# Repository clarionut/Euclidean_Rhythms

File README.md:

# Euclidean Rhythms

This repository contains details of my derivative of [Hagiwo's Euclidean Rhythms](https://note.com/solder_state/n/n433b32ea6dbc) synthesiser module.

In his notes about the module, Hagiwo comments that there is considerable latency due to the OLED display and also mentions instability in the program
possibly caused by memory issues. He partially addresses the latency issue by only updating the OLED on clock inputs, but this makes it difficult to
update the settings in the absence of a clock input.
During analysis of the code I found several things which would compound these issues, e.g.
- use of a relatively slow I2C OLED display. Swapped for an alternative using much faster hardware SPI
- (using a graphics library which keeps an in-memory copy of the display. Changed to the less memory-intensive U8glib library). Subsequent testing has shown that code using the Adafruit_SSD1306 library runs roughly twice as fast as either u8glib or u8g2. I'd therefore recommend using the EuclideanRhythms_AF sketch. It's larger than the u8glib based code but has shown no signs of instability despite its greater functionality
- the original code uses multiple loops over the channels, each processing a single aspect of the code. Restructured to carry out as many of these
operations as possible in a single loop
- use of the Arduino digitalWrite() function (intrinsically very slow) to output the triggers. Replaced by direct port operations to update all trigger
outputs much faster and simultaneously
- the rotary encoder originally used both interrupt pins of the Arduino with simple polling of the clock input, potentially leading to short clock pulses
being missed. The Encoder library can also be used in a single-interrupt mode allowing the clock input to use the other interrupt, with the interrupt
service routine directly generating the trigger outputs

These changes significantly improve the performance and allow the display to be updated on each clock and when the rotary encoder is used. The display
update is still relatively slow even using hardware SPI resulting in long & variable length trigger outputs. Also the OLED is always on even if the
module is not in use. I therefore added a screensaver which blanks the OLED after 30 seconds plus LEDs to monitor the trigger outputs. The OLED is
enabled again when the rotary encoder is used. This allows quite high clock speeds once the screensaver has kicked in.

Some extra functionality has been added to the code:
- ability to 'Put' the current settings into the Arduino EEPROM and 'Get' them from EEPROM in a subsequent session. This version of the code starts up
with predefined default settings, but it would be easy to modify so that the stored settings are retrieved automatically at start up
- a probability control by potentiometer or input CV to vary the likelyhood of changes in Random mode. As in Hagiwo's original code the allowed ranges
of randomness are predefined in the code with the probability controls influencing how likely the changes are
- option for a gate input to re-zero all the output channels to the starting position. I didn't implement this hardware due to a lack of space on my
Eurorack panel but the code for it is present

There are some more details of the changes in the Arduino code comments. The hardware is similar to the original but uses an Arduino Pro Mini rather than
a Nano, has buffering on the outputs for protection and to give higher voltage triggers, and has additional circuitry for the probability controls &
manual step button.

Please note that I built this module using stripboard rather than a PCB. The KiCad files and Gerbers have been used to build an [SPI version of Hagiwo's 6-channel trigger sequencer](https://github.com/clarionut/6-channel-trg-sequencer) so the PCB layout has now been verified apart from the probability CV input section.

### Updates
08-10-2025 - updated KiCad files (amended silk-screen labelling, minor header-pin changes); added Arduino code using the faster Adafruit_SSD1306 library - RECOMMENDED

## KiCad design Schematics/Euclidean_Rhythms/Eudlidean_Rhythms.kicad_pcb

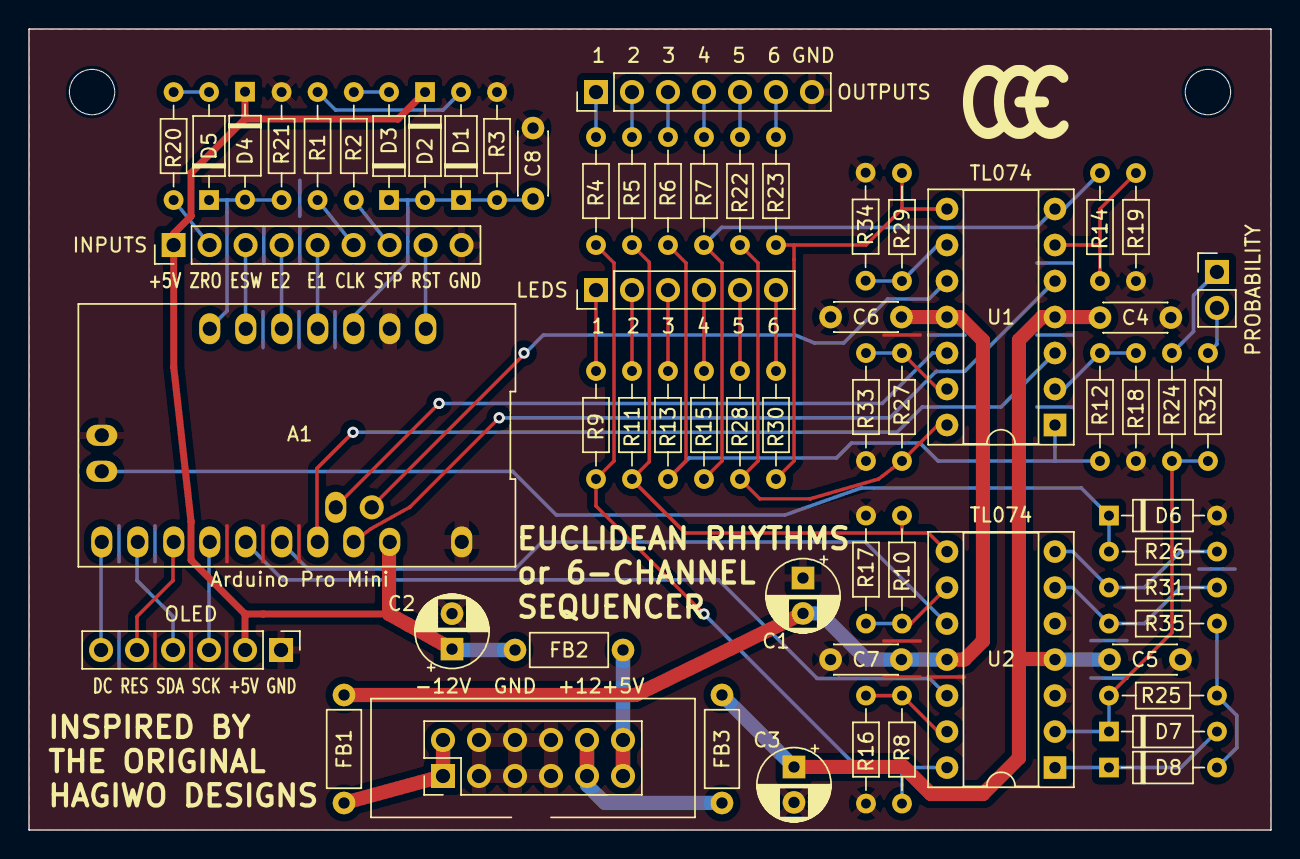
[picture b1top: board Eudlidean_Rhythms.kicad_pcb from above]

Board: 2 copper layers, 87.6 x 56.5 mm, 63 parts (0 on the bottom side), 61 nets.

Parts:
A1: Arduino_Pro_Mini
C1, C2, C3: 10u; CP_Radial_D5.0mm_P2.50mm
C4, C5, C6, C7: 100n; C_Disc_D4.3mm_W1.9mm_P5.00mm
C8: 10n; C_Disc_D4.3mm_W1.9mm_P5.00mm
D1, D2, D3, D4: BAT43; D_DO-35_SOD27_P7.62mm_Horizontal
D5, D7, D8: 1N914; D_DO-35_SOD27_P7.62mm_Horizontal
D6: 5V1; D_DO-35_SOD27_P7.62mm_Horizontal
FB1, FB2, FB3: FB; L_Axial_L5.3mm_D2.2mm_P7.62mm_Horizontal_Vishay_IM-1
J1: POWER; Power_2x06
J2: INPUTS; PinHeader_1x09_P2.54mm_Vertical
J3: LEDS; PinHeader_1x06_P2.54mm_Vertical
J4: PROB; PinHeader_1x02_P2.54mm_Vertical
J5: OUTPUTS; PinHeader_1x07_P2.54mm_Vertical
J6: OLED; PinHeader_1x06_P2.54mm_Vertical
R1, R2, R9, R11, R13, R15, R26, R28, R30: 10k; R_Axial_DIN0204_L3.6mm_D1.6mm_P7.62mm_Horizontal
R3, R16, R17, R18, R19, R20, R21, R24, R25, R31, R32, R33, R34, R35: 100k; R_Axial_DIN0204_L3.6mm_D1.6mm_P7.62mm_Horizontal
R4, R5, R6, R7, R22, R23: 470R; R_Axial_DIN0204_L3.6mm_D1.6mm_P7.62mm_Horizontal
R8, R10, R12, R14, R27, R29: 82k; R_Axial_DIN0204_L3.6mm_D1.6mm_P7.62mm_Horizontal
U1, U2: TL074; DIP-14_W7.62mm_Socket

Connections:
+5V: A1.21 (VCC), C2.1, D2.1 (K), D4.1 (K), FB2.1, J2.1, J6.2
+12V: C3.1, C4.1, C5.1, FB3.1, U1.4 (V+), U2.4 (V+)
-12V: C1.2, C6.1, C7.1, FB1.1, U1.11 (V-), U2.11 (V-)
CLK: J2.6, R1.1
COPI: A1.14 (D11), J6.4
DC: A1.13 (D10), J6.6
E1: A1.6 (D3), J2.5
E2: A1.7 (D4), J2.4
ESW: A1.8 (D5), J2.3
GND: A1.4 (GND), A1.23 (GND), A1.29 (GND), C1.1, C2.2, C3.2, C4.2, C5.2, C6.2, C7.2, C8.1, D6.2 (A), J1.3, J1.4, J1.5, J1.6, J1.7, J1.8, J2.9, J5.7, J6.1, R3.1, R16.1, R17.1, R18.1, R19.1, R21.1, R33.1, R34.1, U2.3 (+), U2.5 (+)
LED1: J3.1, R9.2
LED2: J3.2, R11.2
LED3: J3.3, R13.2
LED4: J3.4, R15.2
LED5: J3.5, R28.2
LED6: J3.6, R30.2
unnamed: A1.17 (A0), U2.12 (+)
unnamed: A1.18 (A1), U2.10 (+)
unnamed: A1.19 (A2), U1.3 (+)
unnamed: A1.20 (A3), U1.5 (+)
unnamed: A1.26 (A4), U1.12 (+)
unnamed: A1.25 (A5), U1.10 (+)
unnamed: A1.28 (A6), D6.1 (K), R26.2
unnamed: A1.9 (D6), D4.2 (A), D5.1 (K), R21.2
unnamed: D1.2 (A), R1.2
unnamed: D3.2 (A), R2.2
unnamed: D5.2 (A), R20.2
unnamed: D7.2 (A), D8.1 (K), U2.1
unnamed: D7.1 (K), R24.2, R25.1, R32.2, U2.2 (-)
unnamed: D8.2 (A), R25.2, R35.1
unnamed: FB1.2, J1.1, J1.2
unnamed: FB3.2, J1.9, J1.10
unnamed: FB2.2, J1.11, J1.12
unnamed: R4.1, R8.2, R9.1, U2.14
unnamed: R5.1, R10.2, R11.1, U2.8
unnamed: R6.1, R12.2, R13.1, U1.1
unnamed: R7.1, R14.2, R15.1, U1.7
unnamed: R22.1, R27.2, R28.1, U1.14
unnamed: R23.1, R29.2, R30.1, U1.8
unnamed: R12.1, R18.2, U1.2 (-)
unnamed: R14.1, R19.2, U1.6 (-)
unnamed: R29.1, R34.2, U1.9 (-)
unnamed: R27.1, R33.2, U1.13 (-)
unnamed: R31.1, R35.2, U2.6 (-)
unnamed: R10.1, R17.2, U2.9 (-)
unnamed: R8.1, R16.2, U2.13 (-)
OUT1: J5.1, R4.2
OUT2: J5.2, R5.2
OUT3: J5.3, R6.2
OUT4: J5.4, R7.2
OUT5: J5.5, R22.2
OUT6: J5.6, R23.2
P1: J4.1, R24.1
P2: J4.2, R32.1
PROB: R26.1, R31.2, U2.7
RES: A1.15 (D12), J6.5
RST: A1.3 (RST), J2.8
SCK: A1.16 (D13), J6.3
STP: J2.7, R2.1
TRG: A1.5 (D2), C8.2, D1.1 (K), D2.2 (A), D3.1 (K), R3.2
ZRO: J2.2, R20.1

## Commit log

2025-06-06 Create temp
2025-06-10 Create tmp
2025-06-10 Rename Euclidean Rhythms.png to Stripboard.png
2025-06-10 Rename Euclidean Rhythms.svg to Stripboard.svg
